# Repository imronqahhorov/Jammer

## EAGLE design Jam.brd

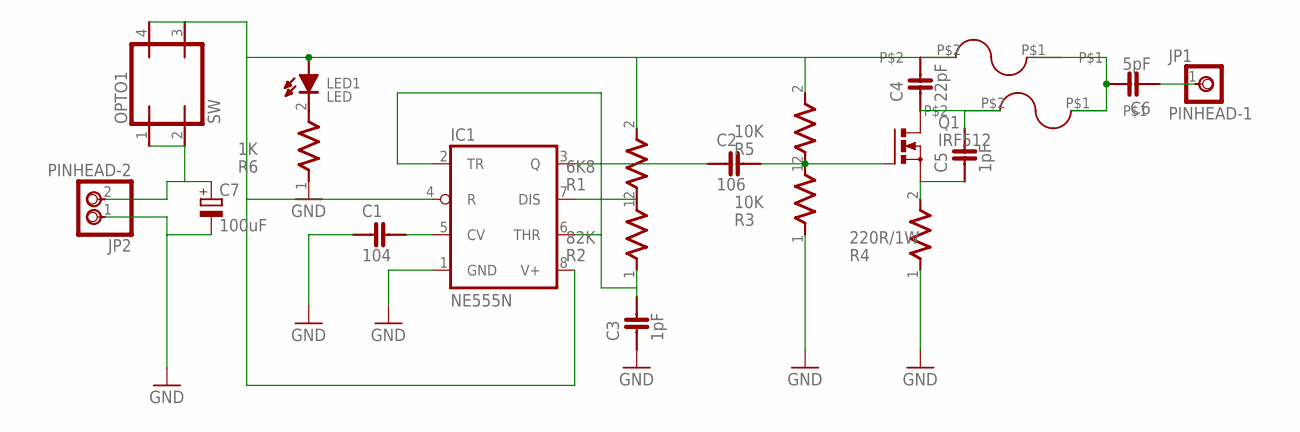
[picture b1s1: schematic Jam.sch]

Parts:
2.2NH: L5
C1: 104; CAP-NP5
C2: 106; CAP-NP5
C3, C5: 1pF; CAP-NP5
C4: 22pF; CAP-NP5
C6: 5pF; CAP-NP5
C7: 100uF; E2,5-7
IC1: NE555N; DIL08
JP1: PINHEAD-1
JP2: PINHEAD-2
LED1: LED; LED5
OPTO1: SW; DIL-04
Q1: IRF512; TO220BV
R1: 6K8; R-7,5
R2: 82K; R-7,5
R3, R5: 10K; R-7,5
R4: 220R/1W; R-10
R6: 1K; R-7,5
U$1: L5

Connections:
GND: C1.1, C3.1, C7.-, IC1.1 (GND), JP2.1, R3.1, R4.1, R6.1
unnamed: C1.2, IC1.5 (CV)
unnamed: 2.2NH.P$2, C4.2, IC1.4 (R), IC1.8 (V+), LED1.A, OPTO1.3 (EMI), OPTO1.4 (COL), R1.2, R5.2
unnamed: C4.1, C5.2, Q1.D, U$1.P$2
unnamed: IC1.7 (DIS), R1.1, R2.2
unnamed: C3.2, IC1.2 (TR), IC1.6 (THR), R2.1
unnamed: 2.2NH.P$1, C6.2, U$1.P$1
unnamed: C2.1, IC1.3 (Q)
unnamed: C5.1, Q1.S, R4.2 (3)
unnamed: C2.2, Q1.G, R3.2, R5.1
unnamed: C6.1, JP1.1
unnamed: C7.+, JP2.2, OPTO1.1 (A), OPTO1.2 (C)
unnamed: LED1.K, R6.2

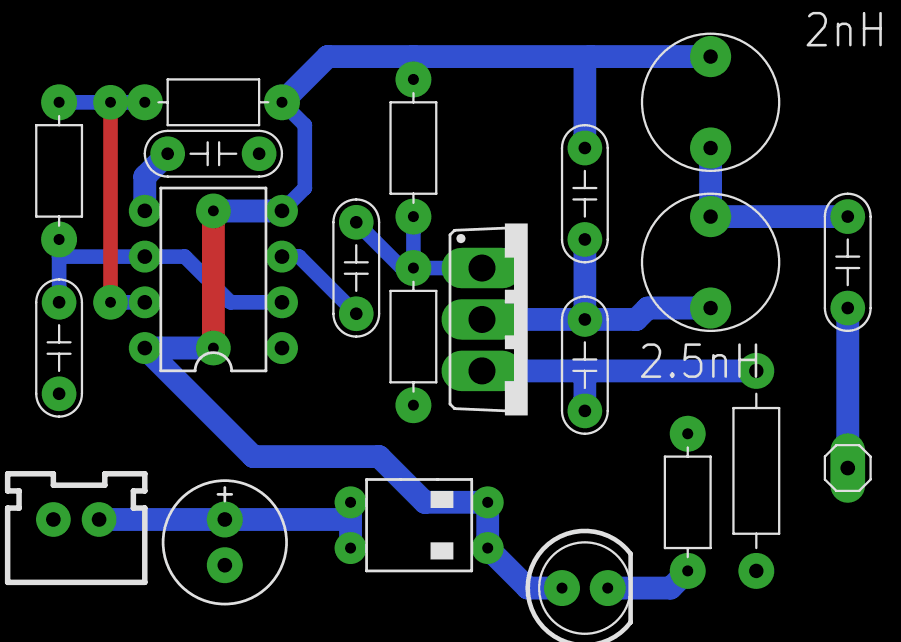
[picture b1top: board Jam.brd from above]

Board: 2 copper layers, 21 parts (0 on the bottom side), 13 nets.
